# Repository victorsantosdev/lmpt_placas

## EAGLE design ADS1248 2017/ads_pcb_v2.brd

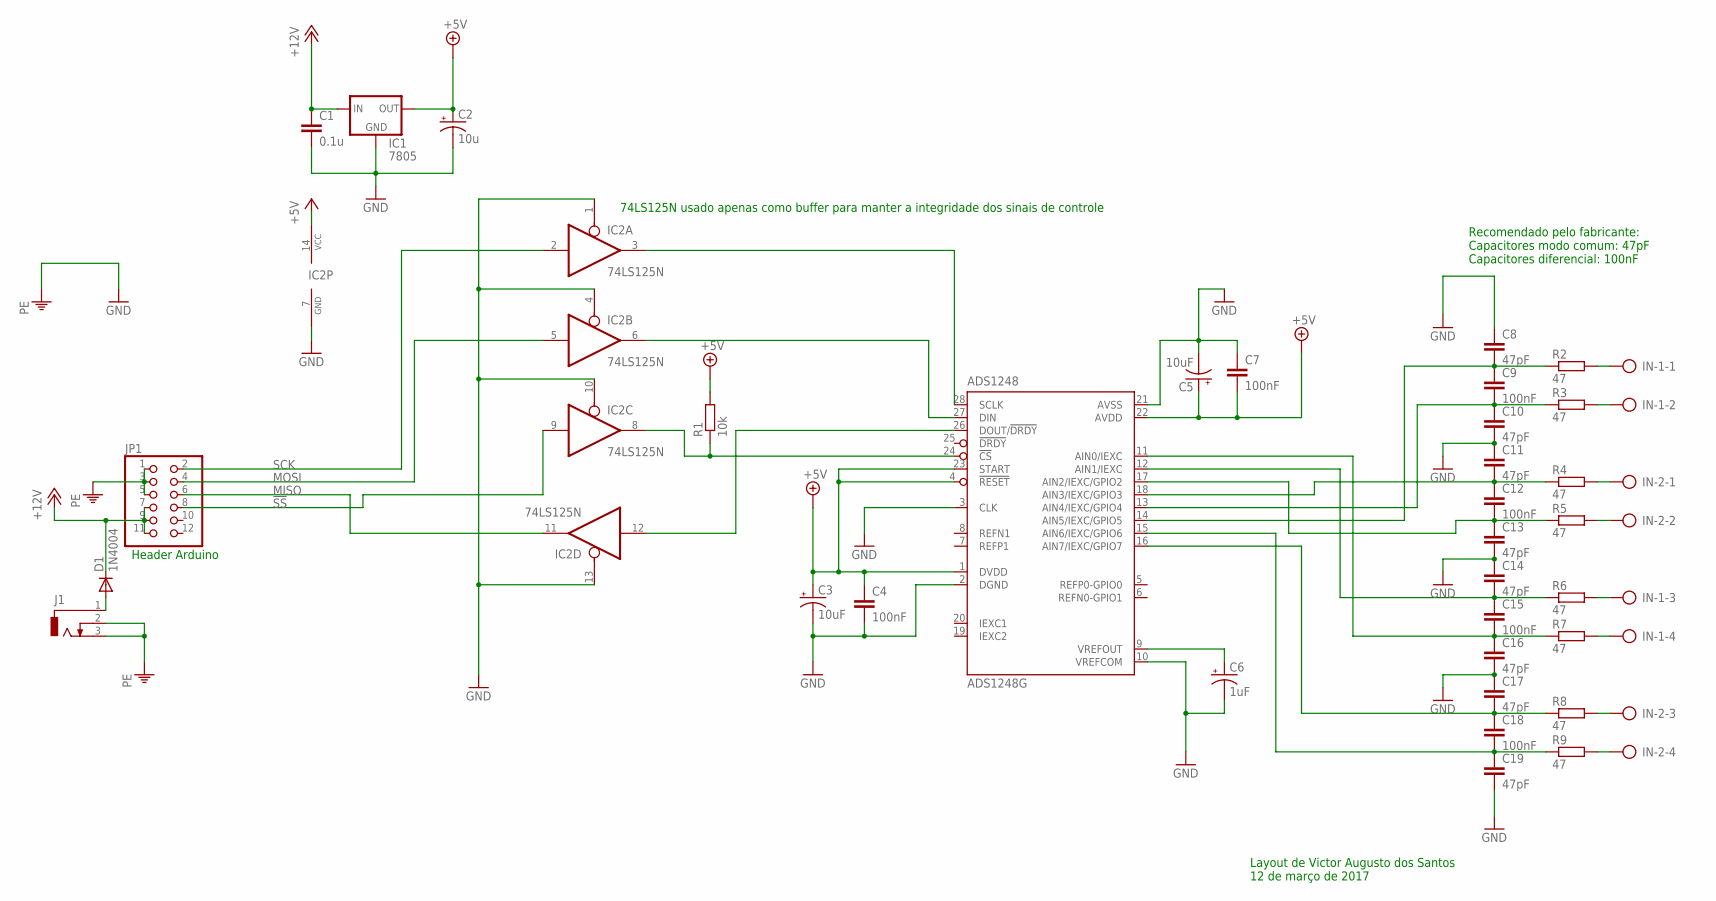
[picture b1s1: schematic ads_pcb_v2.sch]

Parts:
C1: 0.1u; C5B3
C2: 10u; E2-5
C3, C5: 10uF; E2-5
C4, C7: 100nF; C5B3
C6: 1uF; E2-5
C8, C10, C11, C13, C14, C17, C19: 47pF; C5B2.5
C9, C12, C15, C18: 100nF; C5B2.5
C16: 47pF; C5B3
D1: 1N4004; DO41-10
IC1: 7805; 78XXL
IC2: 74LS125N; DIL14
IC3: ADS1248G; P-TSSOP28-1
IN-1, IN-2: AK500/4-H
J1: DCJ0303
JP1: PINHD-2X6; 2X06
R1: 10k; 0204/7
R2, R3, R4, R5, R6, R7, R8, R9: 47; 0204/7

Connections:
!SS: IC2.9 (I), JP1.8
+5V: C2.+, C3.+, C4.1, C5.+, C7.2, IC1.OUT, IC2.14 (VCC), IC3.1 (DVDD), IC3.4 (!RESET), IC3.22 (AVDD), IC3.23 (START), R1.2
+12V: C1.1, D1.C, IC1.IN, JP1.7, JP1.9, JP1.11
GND: C1.2, C2.-, C3.-, C4.2, C5.-, C6.-, C7.1, C8.1, C10.2, C11.1, C13.2, C14.1, C16.2, C17.1, C19.2, IC1.GND, IC2.1 (OE), IC2.4 (OE), IC2.7 (GND), IC2.10 (OE), IC2.13 (OE), IC3.2 (DGND), IC3.3 (CLK), IC3.10 (VREFCOM), IC3.21 (AVSS)
MISO: IC2.11 (O), JP1.6
MOSI: IC2.5 (I), JP1.4
unnamed: C6.+, IC3.9 (VREFOUT)
unnamed: C8.2, C9.1, IC3.14 (AIN5/IEXC/GPIO5), R2.1
unnamed: C9.2, C10.1, IC3.13 (AIN4/IEXC/GPIO4), R3.1
unnamed: IN-2.1, R4.2
unnamed: IC2.3 (O), IC3.28 (SCLK)
unnamed: IN-2.2, R5.2
unnamed: C11.2, C12.1, IC3.18 (AIN3/IEXC/GPIO3), R4.1
unnamed: IN-1.3, R6.2
unnamed: IN-1.4, R7.2
unnamed: IN-2.3, R8.2
unnamed: IC2.6 (O), IC3.27 (DIN)
unnamed: IC2.12 (I), IC3.26 (DOUT/!DRDY)
unnamed: IC2.8 (O), IC3.24 (!CS), R1.1
unnamed: D1.A, J1.1
unnamed: IN-2.4, R9.2
unnamed: IN-1.1, R2.2
unnamed: IN-1.2, R3.2
unnamed: C12.2, C13.1, IC3.17 (AIN2/IEXC/GPIO2), R5.1
unnamed: C17.2, C18.1, IC3.16 (AIN7/IEXC/GPIO7), R8.1
unnamed: C18.2, C19.1, IC3.15 (AIN6/IEXC/GPIO6), R9.1
unnamed: C15.2, C16.1, IC3.11 (AIN0/IEXC), R7.1
unnamed: C14.2, C15.1, IC3.12 (AIN1/IEXC), R6.1
PE: J1.2, J1.3, JP1.1, JP1.3, JP1.5
SCK: IC2.2 (I), JP1.2

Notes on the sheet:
Header Arduino
Recomendado pelo fabricante: Capacitores modo comum: 47pF Capacitores diferencial: 100nF
74LS125N usado apenas como buffer para manter a integridade dos sinais de controle
Layout de Victor Augusto dos Santos 12 de março de 2017

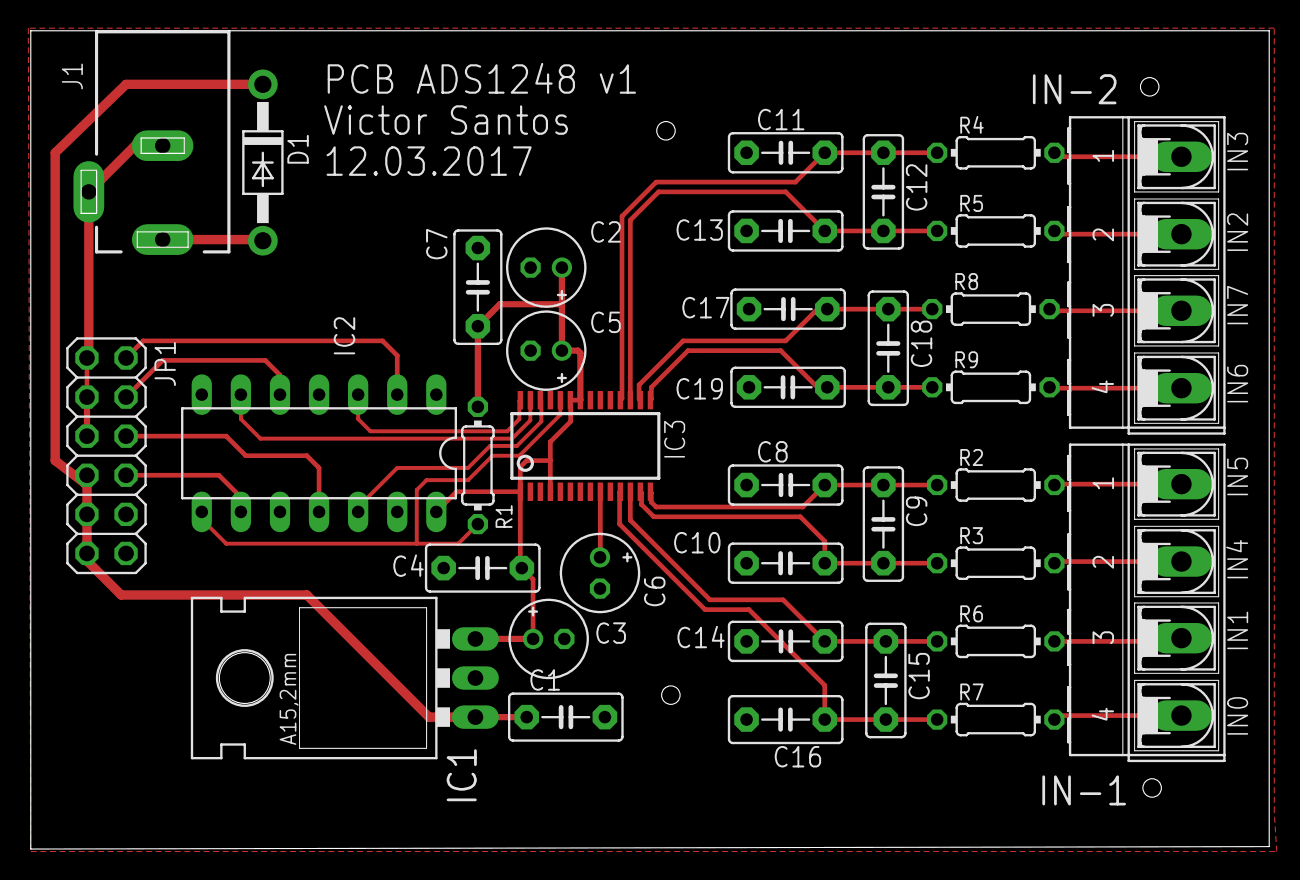
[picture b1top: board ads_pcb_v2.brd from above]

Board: 2 copper layers, 80.5 x 53.2 mm, 36 parts (0 on the bottom side), 30 nets.

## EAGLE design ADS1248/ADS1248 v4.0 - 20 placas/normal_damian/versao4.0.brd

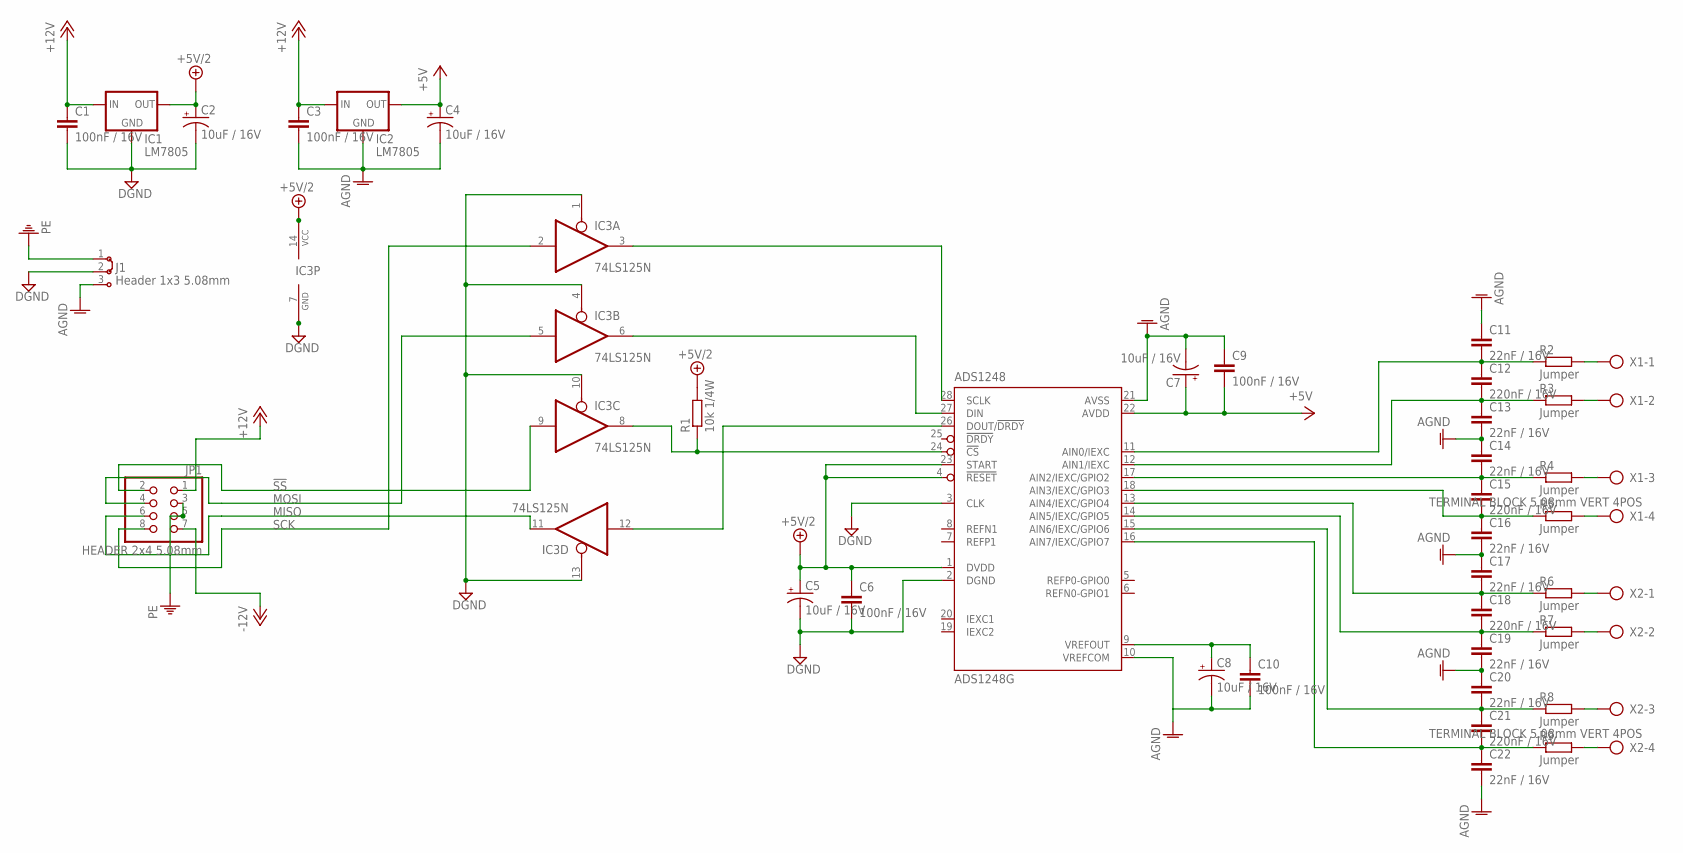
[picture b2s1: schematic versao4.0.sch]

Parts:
C1, C3, C6, C9, C10: 100nF / 16V; C5B3
C2, C4, C5, C7, C8: 10uF / 16V; E2-5
C11, C13, C14, C16, C17, C20, C22: 22nF / 16V; C5B2.5
C12, C15, C18, C21: 220nF / 16V; C5B2.5
C19: 22nF / 16V; C5B3
IC1, IC2: LM7805; 78XXL
IC3: 74LS125N; DIL14
IC4: ADS1248G; P-TSSOP28-1
J1: Header 1x3 5.08mm; 04C
JP1: HEADER 2x4 5.08mm; 2X04
R1: 10k 1/4W; 0204/7
R2, R3, R4, R5, R6, R7, R8, R9: Jumper; 0204/7
X1, X2: TERMINAL BLOCK 5.08mm VERT 4POS; AK500/4-H

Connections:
!SS: IC3.9 (I), JP1.2
+5V: C4.+, C7.+, C9.2, IC2.OUT, IC4.22 (AVDD)
+5V/2: C2.+, C5.+, C6.1, IC1.OUT, IC3.14 (VCC), IC4.1 (DVDD), IC4.4 (!RESET), IC4.23 (START), R1.2
+12V: C1.1, C3.1, IC1.IN, IC2.IN, JP1.1
-12V: JP1.7
AGND: C3.2, C4.-, C7.-, C8.-, C9.1, C10.2, C11.1, C13.2, C14.1, C16.2, C17.1, C19.2, C20.1, C22.2, IC2.GND, IC4.10 (VREFCOM), IC4.21 (AVSS), J1.3
DGND: C1.2, C2.-, C5.-, C6.2, IC1.GND, IC3.1 (OE), IC3.4 (OE), IC3.7 (GND), IC3.10 (OE), IC3.13 (OE), IC4.2 (DGND), IC4.3 (CLK), J1.2
MISO: IC3.11 (O), JP1.6
MOSI: IC3.5 (I), JP1.4
unnamed: C8.+, C10.1, IC4.9 (VREFOUT)
unnamed: C11.2, C12.1, IC4.11 (AIN0/IEXC), R2.1
unnamed: C12.2, C13.1, IC4.12 (AIN1/IEXC), R3.1
unnamed: R3.2, X1.2
unnamed: IC3.3 (O), IC4.28 (SCLK)
unnamed: R9.2, X2.4
unnamed: C17.2, C18.1, IC4.13 (AIN4/IEXC/GPIO4), R6.1
unnamed: C20.2, C21.1, IC4.15 (AIN6/IEXC/GPIO6), R8.1
unnamed: C18.2, C19.1, IC4.14 (AIN5/IEXC/GPIO5), R7.1
unnamed: C15.2, C16.1, IC4.18 (AIN3/IEXC/GPIO3), R5.1
unnamed: IC3.6 (O), IC4.27 (DIN)
unnamed: IC3.12 (I), IC4.26 (DOUT/!DRDY)
unnamed: IC3.8 (O), IC4.24 (!CS), R1.1
unnamed: R2.2, X1.1
unnamed: R8.2, X2.3
unnamed: R7.2, X2.2
unnamed: R6.2, X2.1
unnamed: R5.2, X1.4
unnamed: R4.2, X1.3
unnamed: C21.2, C22.1, IC4.16 (AIN7/IEXC/GPIO7), R9.1
unnamed: C14.2, C15.1, IC4.17 (AIN2/IEXC/GPIO2), R4.1
PE: J1.1, JP1.3, JP1.5
SCK: IC3.2 (I), JP1.8

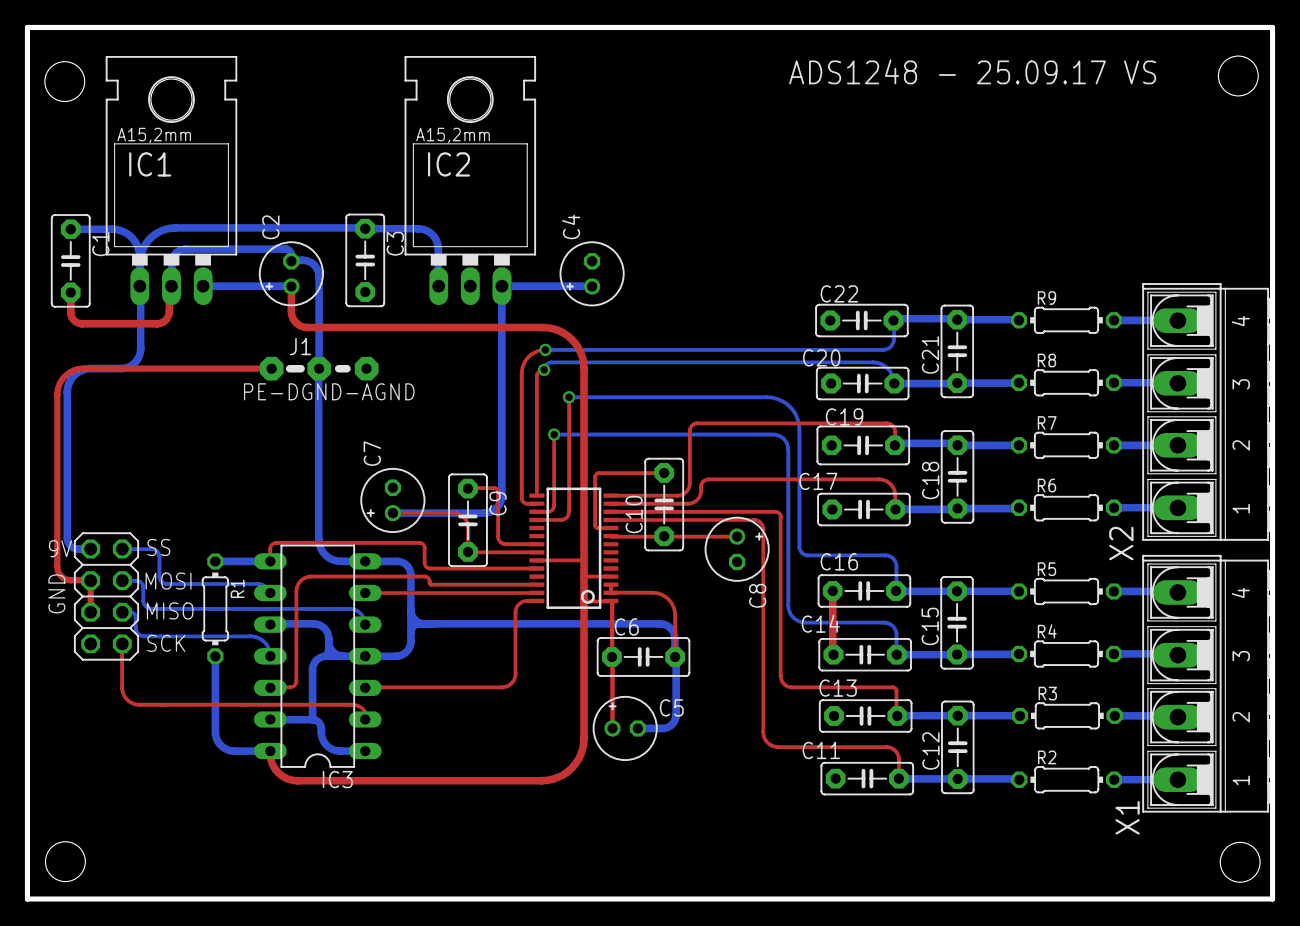
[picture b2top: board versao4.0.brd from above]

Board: 2 copper layers, 100.0 x 70.0 mm, 39 parts (0 on the bottom side), 31 nets.

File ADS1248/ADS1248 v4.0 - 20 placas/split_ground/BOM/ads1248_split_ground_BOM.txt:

Partlist exported from C:/Users/win10/Documents/eagle/Git LMPT Placas/ADS1248/ADS1248 v4.0 - 20 placas/split_ground/versao4.0.sch at 29/09/2017 10:56

Qty Value                           Device      Package     Parts                             Description                          
5   100nF/16V                       C5/3        C5B3        C1, C3, C6, C9, C10               CAPACITOR                            
1   10K 1/4W                        R-EU_0204/7 0204/7      R1                                RESISTOR, European symbol            
5   10uF/16V                        CPOL-USE2-5 E2-5        C2, C4, C5, C7, C8                POLARIZED CAPACITOR, American symbol 
4   220nF/16V                       C5/2.5      C5B2.5      C12, C15, C18, C21                CAPACITOR                            
7   22nF/16V                        C5/2.5      C5B2.5      C11, C13, C14, C16, C17, C20, C22 CAPACITOR                            
1   22nF/16V                        C5/3        C5B3        C19                               CAPACITOR                            
1   74LS125N                        74LS125N    DIL14       IC3                               Quad bus BUFFER, 3-state             
2   7805                            78XXL       78XXL       IC1, IC2                          VOLTAGE REGULATOR                    
1   ADS1248G                        ADS1248G    P-TSSOP28-1 IC4                               Phase locked loop                    
1   HEADER 2x4 5.08mm               PINHD-2X4   2X04        JP1                               PIN HEADER                           
2   TERMINAL BLOCK 5.08MM VERT 4POS AK500/4-H   AK500/4-H   X1, X2                            CONNECTOR                            
8   Wire                            R-EU_0204/7 0204/7      R2, R3, R4, R5, R6, R7, R8, R9    RESISTOR, European symbol
